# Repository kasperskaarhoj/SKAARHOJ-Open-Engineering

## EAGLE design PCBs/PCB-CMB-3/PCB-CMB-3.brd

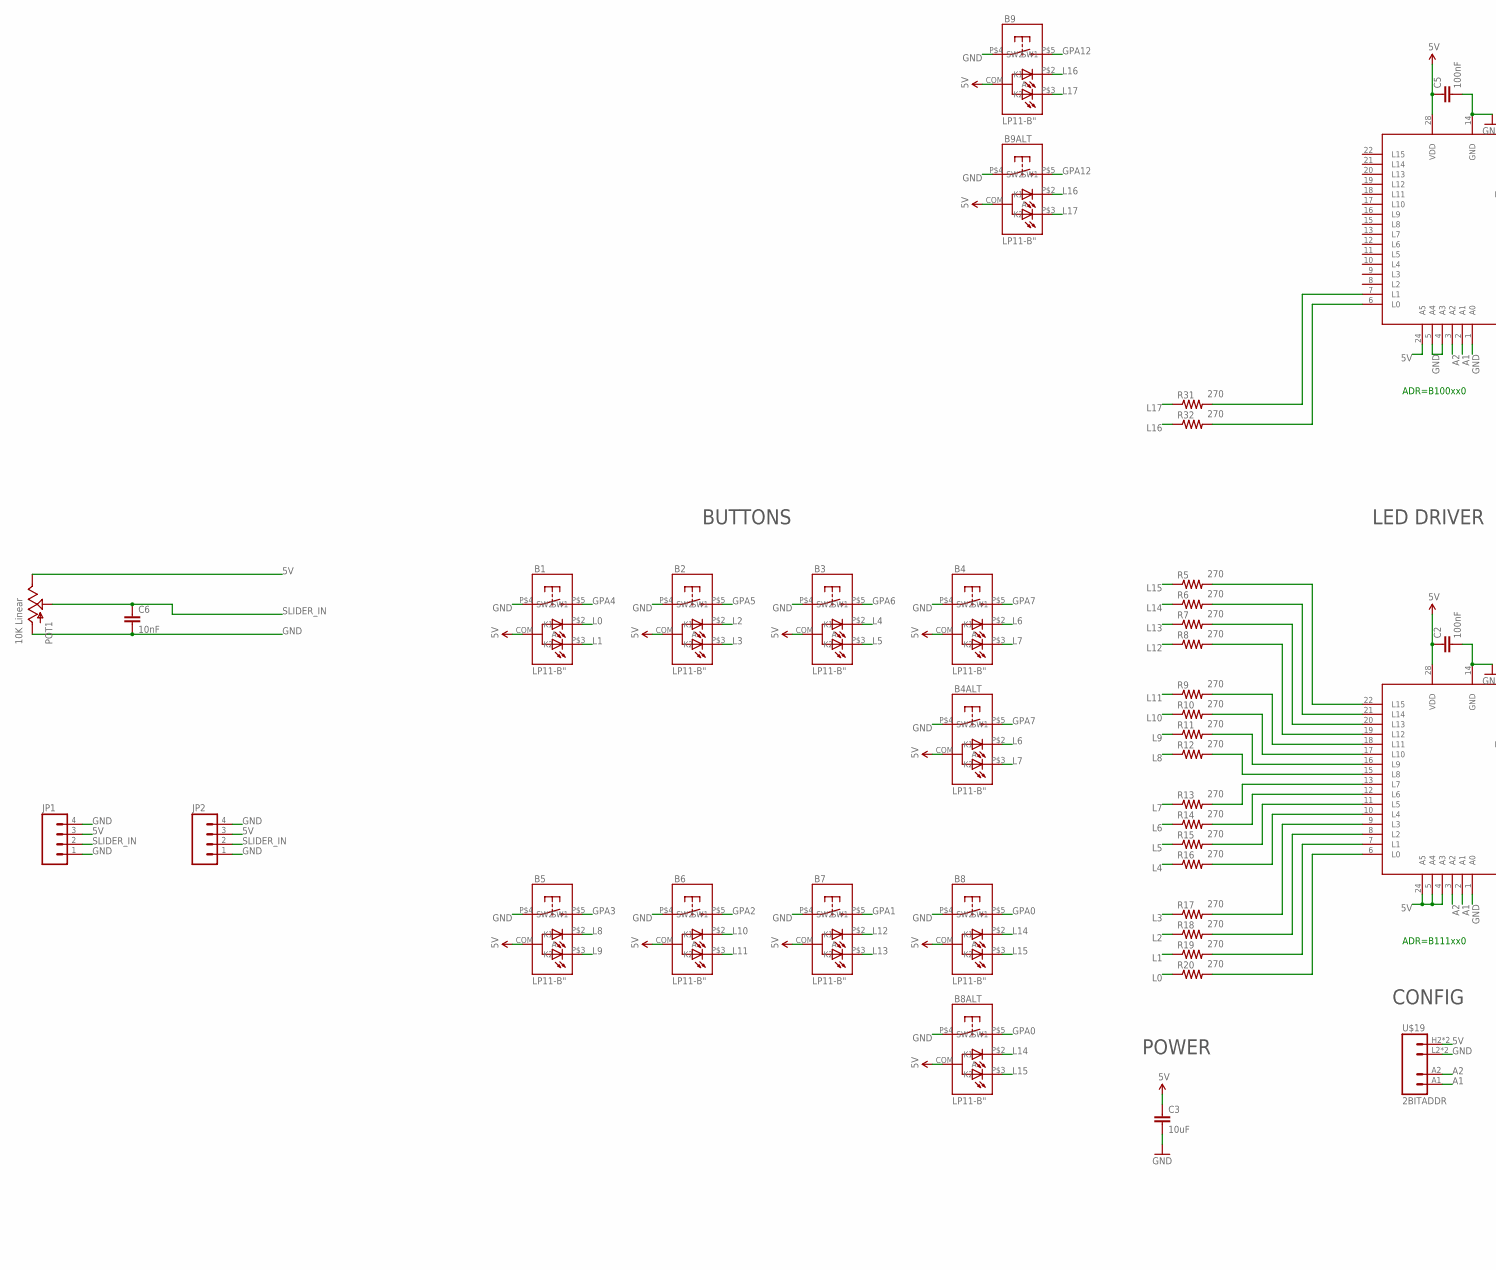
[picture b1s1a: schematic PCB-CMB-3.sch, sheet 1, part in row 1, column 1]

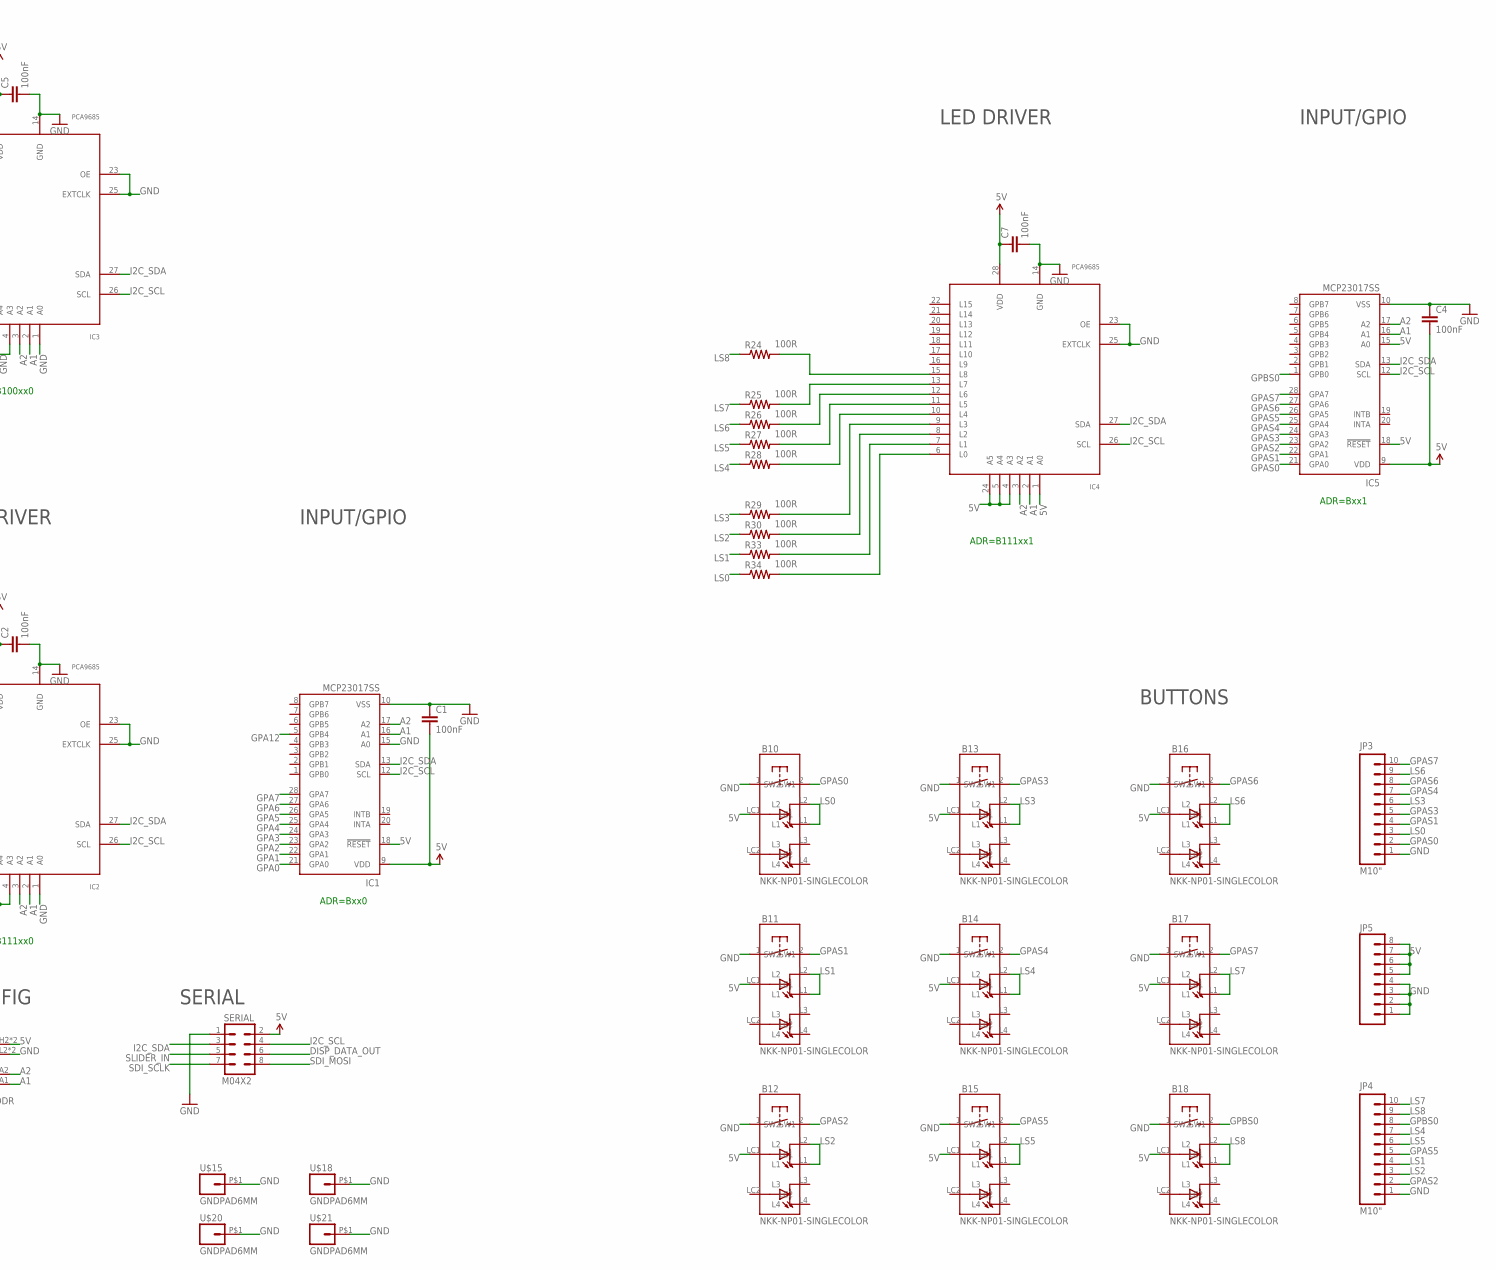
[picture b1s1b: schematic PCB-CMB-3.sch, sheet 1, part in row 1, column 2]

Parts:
B1, B2, B3, B4, B4ALT, B5, B6, B7, B8, B8ALT, B9, B9ALT: LP11-B"; LP11
B10, B11, B12, B13, B14, B15, B16, B17, B18: NKK-NP01-SINGLECOLOR; NKK-NP01
C1, C2, C4, C5, C7: 100nF; 0603-CAP
C3: 10uF; 0805
C6: 10nF; 0603-CAP
IC1, IC5: MCP23017SS; SSOP28; MPN MCP23017-E/SS
IC2, IC3, IC4: PCA9685; TSSOP28
JP1, JP2: M04PTH; 1X04
JP3, JP4: M10"; 1X10
JP5: M08LOCK; 1X08_LOCK
POT1: 10K Linear; SLIDER20
R5, R6, R7, R8, R9, R10, R11, R12, R13, R14, R15, R16, R17, R18, R19, R20, R31, R32: 270; 0603-RES
R24, R25, R26, R27, R28, R29, R30, R33, R34: 100R; 0603-RES
SERIAL: M04X2; 2X4
U$15, U$18, U$20, U$21: GNDPAD6MM; 3.2MMPAD6MM
U$19: 2BITADDR

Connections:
5V: B1.COM (A), B2.COM (A), B3.COM (A), B4.COM (A), B4ALT.COM (A), B5.COM (A), B6.COM (A), B7.COM (A), B8.COM (A), B8ALT.COM (A), B9.COM (A), B9ALT.COM (A), B10.LC1, B11.LC1, B12.LC1, B13.LC1, B14.LC1, B15.LC1, B16.LC1, B17.LC1, B18.LC1, C1.2, C2.1, C3.1, C4.2, C5.1, C7.1, IC1.9 (VDD), IC1.18 (!RESET), IC2.4 (A3), IC2.5 (A4), IC2.24 (A5), IC2.28 (VDD), IC3.24 (A5), IC3.28 (VDD), IC4.1 (A0), IC4.4 (A3), IC4.5 (A4), IC4.24 (A5), IC4.28 (VDD), IC5.9 (VDD), IC5.15 (A0), IC5.18 (!RESET), JP1.3, JP2.3, JP5.5, JP5.6, JP5.7, JP5.8, POT1.1 (E), SERIAL.2, U$19.H2 (VCC), U$19.H3 (VCC)
A1: IC1.16 (A1), IC2.2 (A1), IC3.2 (A1), IC4.2 (A1), IC5.16 (A1), U$19.A1
A2: IC1.17 (A2), IC2.3 (A2), IC3.3 (A2), IC4.3 (A2), IC5.17 (A2), U$19.A2
DISP_DATA_OUT: SERIAL.6
GND: B1.P$4 (SW1), B2.P$4 (SW1), B3.P$4 (SW1), B4.P$4 (SW1), B4ALT.P$4 (SW1), B5.P$4 (SW1), B6.P$4 (SW1), B7.P$4 (SW1), B8.P$4 (SW1), B8ALT.P$4 (SW1), B9.P$4 (SW1), B9ALT.P$4 (SW1), B10.1 (SW1), B11.1 (SW1), B12.1 (SW1), B13.1 (SW1), B14.1 (SW1), B15.1 (SW1), B16.1 (SW1), B17.1 (SW1), B18.1 (SW1), C1.1, C2.2, C3.2, C4.1, C5.2, C6.2, C7.2, IC1.10 (VSS), IC1.15 (A0), IC2.1 (A0), IC2.14 (GND), IC2.23 (OE), IC2.25 (EXTCLK), IC3.1 (A0), IC3.4 (A3), IC3.5 (A4), IC3.14 (GND), IC3.23 (OE), IC3.25 (EXTCLK), IC4.14 (GND), IC4.23 (OE), IC4.25 (EXTCLK), IC5.10 (VSS), JP1.1, JP1.4, JP2.1, JP2.4, JP3.1, JP4.1, JP5.1, JP5.2, JP5.3, JP5.4, POT1.3 (A), SERIAL.1, U$15.P$1, U$18.P$1, U$19.L2 (GND), U$19.L3 (GND), U$20.P$1, U$21.P$1
GPA0: B8.P$5 (SW2), B8ALT.P$5 (SW2), IC1.21 (GPA0)
GPA1: B7.P$5 (SW2), IC1.22 (GPA1)
GPA2: B6.P$5 (SW2), IC1.23 (GPA2)
GPA3: B5.P$5 (SW2), IC1.24 (GPA3)
GPA4: B1.P$5 (SW2), IC1.25 (GPA4)
GPA5: B2.P$5 (SW2), IC1.26 (GPA5)
GPA6: B3.P$5 (SW2), IC1.27 (GPA6)
GPA7: B4.P$5 (SW2), B4ALT.P$5 (SW2), IC1.28 (GPA7)
GPA12: B9.P$5 (SW2), B9ALT.P$5 (SW2), IC1.5 (GPB4)
GPAS0: B10.2 (SW2), IC5.21 (GPA0), JP3.2
GPAS1: B11.2 (SW2), IC5.22 (GPA1), JP3.4
GPAS2: B12.2 (SW2), IC5.23 (GPA2), JP4.2
GPAS3: B13.2 (SW2), IC5.24 (GPA3), JP3.5
GPAS4: B14.2 (SW2), IC5.25 (GPA4), JP3.7
GPAS5: B15.2 (SW2), IC5.26 (GPA5), JP4.5
GPAS6: B16.2 (SW2), IC5.27 (GPA6), JP3.8
GPAS7: B17.2 (SW2), IC5.28 (GPA7), JP3.10
GPBS0: B18.2 (SW2), IC5.1 (GPB0), JP4.8
I2C_SCL: IC1.12 (SCL), IC2.26 (SCL), IC3.26 (SCL), IC4.26 (SCL), IC5.12 (SCL), SERIAL.4
I2C_SDA: IC1.13 (SDA), IC2.27 (SDA), IC3.27 (SDA), IC4.27 (SDA), IC5.13 (SDA), SERIAL.3
L0: B1.P$2 (K1), R20.1
L1: B1.P$3 (K2), R19.1
L2: B2.P$2 (K1), R18.1
L3: B2.P$3 (K2), R17.1
L4: B3.P$2 (K1), R16.1
L5: B3.P$3 (K2), R15.1
L6: B4.P$2 (K1), B4ALT.P$2 (K1), R14.1
L7: B4.P$3 (K2), B4ALT.P$3 (K2), R13.1
L8: B5.P$2 (K1), R12.1
L9: B5.P$3 (K2), R11.1
L10: B6.P$2 (K1), R10.1
L11: B6.P$3 (K2), R9.1
L12: B7.P$2 (K1), R8.1
L13: B7.P$3 (K2), R7.1
L14: B8.P$2 (K1), B8ALT.P$2 (K1), R6.1
L15: B8.P$3 (K2), B8ALT.P$3 (K2), R5.1
L16: B9.P$2 (K1), B9ALT.P$2 (K1), R32.1
L17: B9.P$3 (K2), B9ALT.P$3 (K2), R31.1
LS0: B10.L1, B10.L2, JP3.3, R34.1
LS1: B11.L1, B11.L2, JP4.4, R33.1
LS2: B12.L1, B12.L2, JP4.3, R30.1
LS3: B13.L1, B13.L2, JP3.6, R29.1
LS4: B14.L1, B14.L2, JP4.7, R28.1
LS5: B15.L1, B15.L2, JP4.6, R27.1
LS6: B16.L1, B16.L2, JP3.9, R26.1
LS7: B17.L1, B17.L2, JP4.10, R25.1
LS8: B18.L1, B18.L2, JP4.9, R24.1
unnamed: IC4.13 (L7), R25.2
unnamed: IC4.12 (L6), R26.2
unnamed: IC4.11 (L5), R27.2
unnamed: IC2.13 (L7), R13.2
unnamed: IC2.12 (L6), R14.2
unnamed: IC4.10 (L4), R28.2
unnamed: IC2.11 (L5), R15.2
unnamed: IC4.9 (L3), R29.2
unnamed: IC2.10 (L4), R16.2
unnamed: IC2.9 (L3), R17.2
unnamed: IC2.8 (L2), R18.2
unnamed: IC2.7 (L1), R19.2
unnamed: IC4.8 (L2), R30.2
unnamed: IC3.7 (L1), R31.2
unnamed: IC3.6 (L0), R32.2
unnamed: IC4.7 (L1), R33.2
unnamed: IC4.6 (L0), R34.2
unnamed: IC4.15 (L8), R24.2
unnamed: IC2.6 (L0), R20.2
unnamed: IC2.15 (L8), R12.2
unnamed: IC2.16 (L9), R11.2
unnamed: IC2.17 (L10), R10.2
unnamed: IC2.18 (L11), R9.2
unnamed: IC2.19 (L12), R8.2
unnamed: IC2.20 (L13), R7.2
unnamed: IC2.21 (L14), R6.2
unnamed: IC2.22 (L15), R5.2
SDI_MOSI: SERIAL.8
SDI_SCLK: SERIAL.7
SLIDER_IN: C6.1, JP1.2, JP2.2, POT1.2A (S), SERIAL.5

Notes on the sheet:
ADR=B111xx0
ADR=Bxx0
BUTTONS
LED DRIVER
INPUT/GPIO
POWER
SERIAL
CONFIG
ADR=B100xx0
ADR=B111xx1
ADR=Bxx1

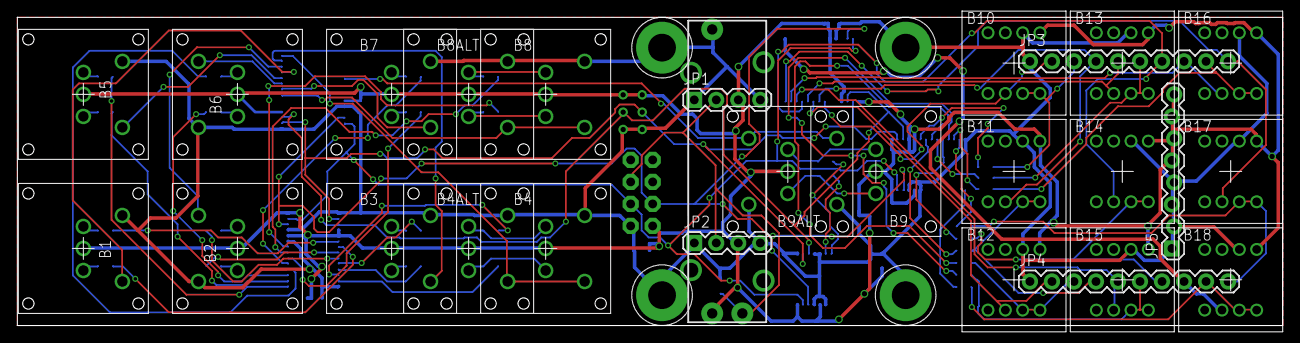
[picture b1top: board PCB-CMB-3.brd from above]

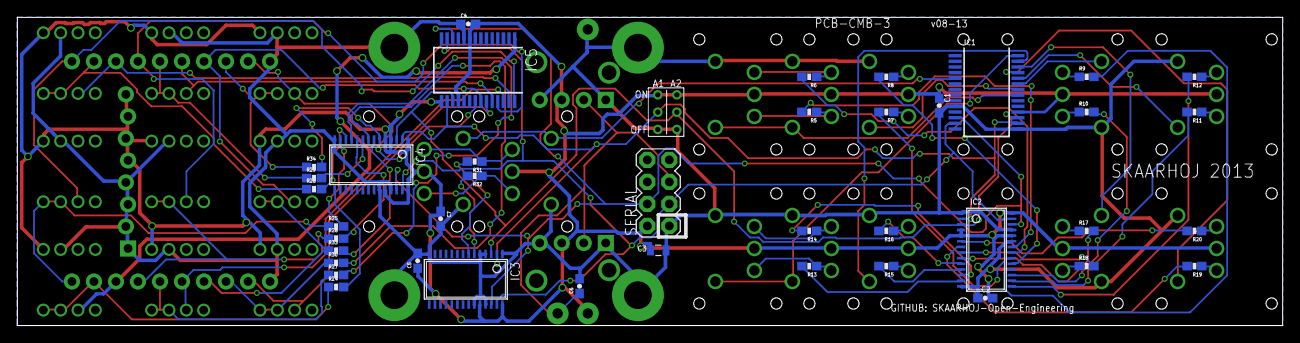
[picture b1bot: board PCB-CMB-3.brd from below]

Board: 2 copper layers, 146.0 x 35.6 mm, 72 parts (41 on the bottom side), 79 nets.

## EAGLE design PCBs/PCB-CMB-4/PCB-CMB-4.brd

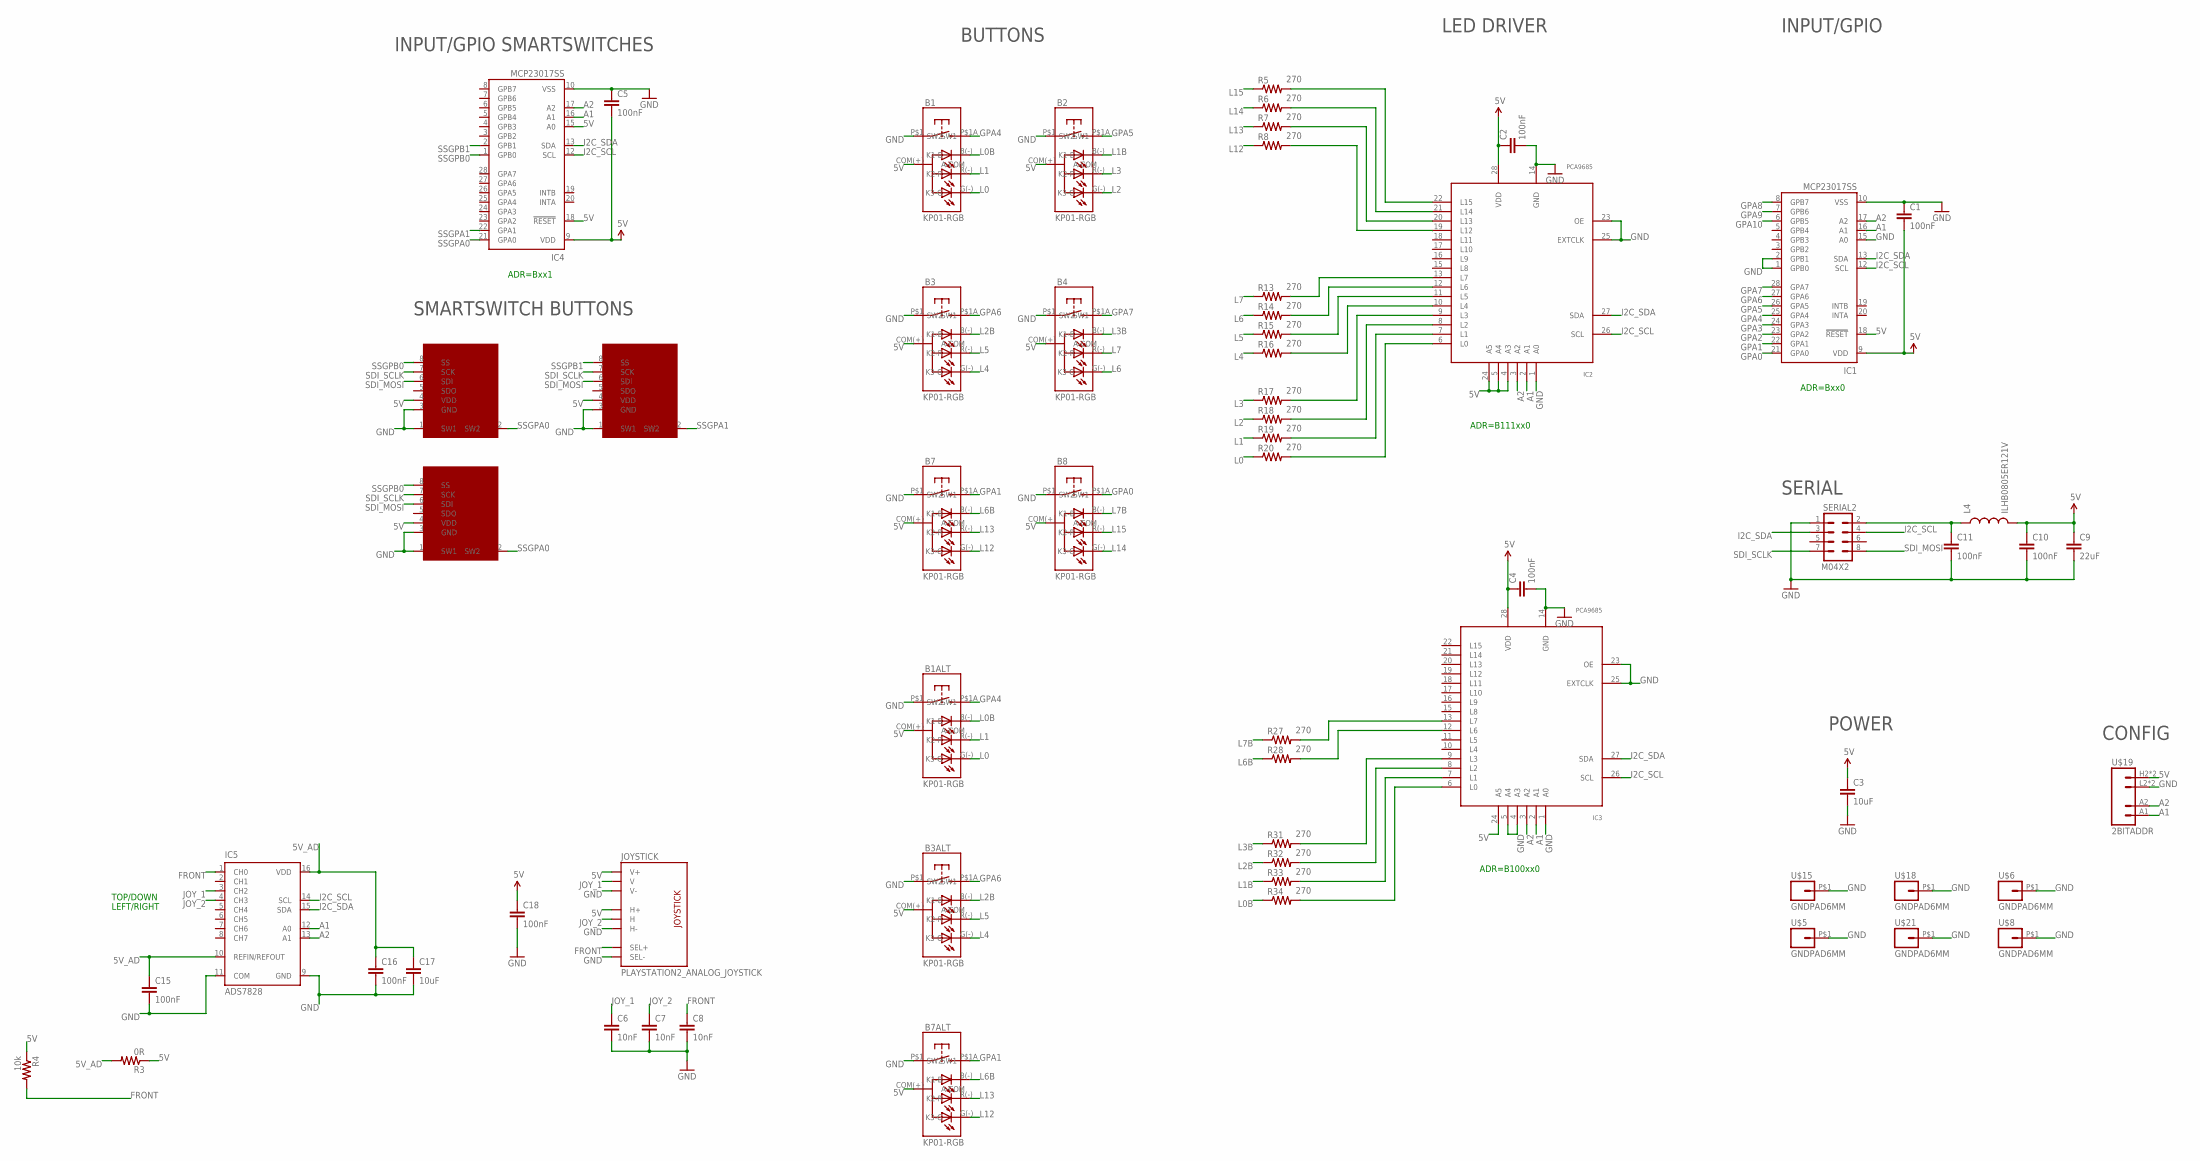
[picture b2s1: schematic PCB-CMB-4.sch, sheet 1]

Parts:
B1, B1ALT, B2, B3, B3ALT, B4, B7, B7ALT, B8: KP01-RGB; NKK-KP01
C1, C2, C4, C5, C10, C11, C15, C16, C18: 100nF; 0603-CAP
C3, C17: 10uF; 0805
C6, C7, C8: 10nF; 0603-CAP
C9: 22uF; 0805
IC1, IC4: MCP23017SS; SSOP28; MPN MCP23017-E/SS
IC2, IC3: PCA9685; TSSOP28
IC5: ADS7828; TSSOP16-PW
JOYSTICK: PLAYSTATION2_ANALOG_JOYSTICK
L4: ILHB0805ER121V; 0805
R3: 0R; 0603-RES
R4: 10k; 0603-RES
R5, R6, R7, R8, R13, R14, R15, R16, R17, R18, R19, R20, R27, R28, R31, R32, R33, R34: 270; 0603-RES
SERIAL2: M04X2; 2X4
SSW1, SSW1ALT, SSW2: SMART_SWITCHSMART_SWITCH_8PIN; SMART_SWITCH
U$5, U$6, U$8, U$15, U$18, U$21: GNDPAD6MM; 3.2MMPAD6MM
U$19: 2BITADDR

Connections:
5V: B1.COM(+) (A-COM), B1ALT.COM(+) (A-COM), B2.COM(+) (A-COM), B3.COM(+) (A-COM), B3ALT.COM(+) (A-COM), B4.COM(+) (A-COM), B7.COM(+) (A-COM), B7ALT.COM(+) (A-COM), B8.COM(+) (A-COM), C1.2, C2.1, C3.1, C4.1, C5.2, C9.1, C10.1, C18.1, IC1.9 (VDD), IC1.18 (!RESET), IC2.4 (A3), IC2.5 (A4), IC2.24 (A5), IC2.28 (VDD), IC3.24 (A5), IC3.28 (VDD), IC4.9 (VDD), IC4.15 (A0), IC4.18 (!RESET), JOYSTICK.H1 (H+), JOYSTICK.V1 (V+), L4.2, R3.1, R4.1, SSW1.4 (VDD), SSW1ALT.4 (VDD), SSW2.4 (VDD), U$19.H2 (VCC), U$19.H3 (VCC)
5V_AD: C15.1, C16.1, C17.1, IC5.10 (REFIN/REFOUT), IC5.16 (VDD), R3.2
A1: IC1.16 (A1), IC2.2 (A1), IC3.2 (A1), IC4.16 (A1), IC5.12 (A0), U$19.A1
A2: IC1.17 (A2), IC2.3 (A2), IC3.3 (A2), IC4.17 (A2), IC5.13 (A1), U$19.A2
FRONT: C8.1, IC5.1 (CH0), JOYSTICK.B1A (SEL+), R4.2
GND: B1.P$1 (SW1), B1ALT.P$1 (SW1), B2.P$1 (SW1), B3.P$1 (SW1), B3ALT.P$1 (SW1), B4.P$1 (SW1), B7.P$1 (SW1), B7ALT.P$1 (SW1), B8.P$1 (SW1), C1.1, C2.2, C3.2, C4.2, C5.1, C6.2, C7.2, C8.2, C9.2, C10.2, C11.2, C15.2, C16.2, C17.2, C18.2, IC1.1 (GPB0), IC1.2 (GPB1), IC1.10 (VSS), IC1.15 (A0), IC2.1 (A0), IC2.14 (GND), IC2.23 (OE), IC2.25 (EXTCLK), IC3.1 (A0), IC3.4 (A3), IC3.5 (A4), IC3.14 (GND), IC3.23 (OE), IC3.25 (EXTCLK), IC4.10 (VSS), IC5.9 (GND), IC5.11 (COM), JOYSTICK.B2A (SEL-), JOYSTICK.H3 (H-), JOYSTICK.V3 (V-), SERIAL2.1, SSW1.1 (SW1), SSW1.3 (GND), SSW1ALT.1 (SW1), SSW1ALT.3 (GND), SSW2.1 (SW1), SSW2.3 (GND), U$5.P$1, U$6.P$1, U$8.P$1, U$15.P$1, U$18.P$1, U$19.L2 (GND), U$19.L3 (GND), U$21.P$1
GPA0: B8.P$1A (SW2), IC1.21 (GPA0)
GPA1: B7.P$1A (SW2), B7ALT.P$1A (SW2), IC1.22 (GPA1)
GPA2: IC1.23 (GPA2)
GPA3: IC1.24 (GPA3)
GPA4: B1.P$1A (SW2), B1ALT.P$1A (SW2), IC1.25 (GPA4)
GPA5: B2.P$1A (SW2), IC1.26 (GPA5)
GPA6: B3.P$1A (SW2), B3ALT.P$1A (SW2), IC1.27 (GPA6)
GPA7: B4.P$1A (SW2), IC1.28 (GPA7)
GPA8: IC1.8 (GPB7)
GPA9: IC1.7 (GPB6)
GPA10: IC1.6 (GPB5)
I2C_SCL: IC1.12 (SCL), IC2.26 (SCL), IC3.26 (SCL), IC4.12 (SCL), IC5.14 (SCL), SERIAL2.4
I2C_SDA: IC1.13 (SDA), IC2.27 (SDA), IC3.27 (SDA), IC4.13 (SDA), IC5.15 (SDA), SERIAL2.3
JOY_1: C6.1, IC5.3 (CH2), JOYSTICK.V2 (V)
JOY_2: C7.1, IC5.4 (CH3), JOYSTICK.H2 (H)
L0: B1.G(-) (K3-G), B1ALT.G(-) (K3-G), R20.1
L0B: B1.B(-) (K1-B), B1ALT.B(-) (K1-B), R34.1
L1: B1.R(-) (K2-R), B1ALT.R(-) (K2-R), R19.1
L1B: B2.B(-) (K1-B), R33.1
L2: B2.G(-) (K3-G), R18.1
L2B: B3.B(-) (K1-B), B3ALT.B(-) (K1-B), R32.1
L3: B2.R(-) (K2-R), R17.1
L3B: B4.B(-) (K1-B), R31.1
L4: B3.G(-) (K3-G), B3ALT.G(-) (K3-G), R16.1
L5: B3.R(-) (K2-R), B3ALT.R(-) (K2-R), R15.1
L6: B4.G(-) (K3-G), R14.1
L6B: B7.B(-) (K1-B), B7ALT.B(-) (K1-B), R28.1
L7: B4.R(-) (K2-R), R13.1
L7B: B8.B(-) (K1-B), R27.1
L12: B7.G(-) (K3-G), B7ALT.G(-) (K3-G), R8.1
L13: B7.R(-) (K2-R), B7ALT.R(-) (K2-R), R7.1
L14: B8.G(-) (K3-G), R6.1
L15: B8.R(-) (K2-R), R5.1
unnamed: C11.1, L4.1, SERIAL2.2
unnamed: IC3.13 (L7), R27.2
unnamed: IC3.12 (L6), R28.2
unnamed: IC2.13 (L7), R13.2
unnamed: IC2.12 (L6), R14.2
unnamed: IC2.11 (L5), R15.2
unnamed: IC2.10 (L4), R16.2
unnamed: IC2.9 (L3), R17.2
unnamed: IC2.8 (L2), R18.2
unnamed: IC2.7 (L1), R19.2
unnamed: IC3.9 (L3), R31.2
unnamed: IC3.8 (L2), R32.2
unnamed: IC3.7 (L1), R33.2
unnamed: IC3.6 (L0), R34.2
unnamed: IC2.6 (L0), R20.2
unnamed: IC2.19 (L12), R8.2
unnamed: IC2.20 (L13), R7.2
unnamed: IC2.21 (L14), R6.2
unnamed: IC2.22 (L15), R5.2
SDI_MOSI: SERIAL2.8, SSW1.6 (SDI), SSW1ALT.6 (SDI), SSW2.6 (SDI)
SDI_SCLK: SERIAL2.7, SSW1.7 (SCK), SSW1ALT.7 (SCK), SSW2.7 (SCK)
SSGPA0: IC4.21 (GPA0), SSW1.2 (SW2), SSW1ALT.2 (SW2)
SSGPA1: IC4.22 (GPA1), SSW2.2 (SW2)
SSGPB0: IC4.1 (GPB0), SSW1.8 (SS), SSW1ALT.8 (SS)
SSGPB1: IC4.2 (GPB1), SSW2.8 (SS)

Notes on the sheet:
ADR=B111xx0
ADR=Bxx0
BUTTONS
LED DRIVER
INPUT/GPIO
POWER
ADR=B100xx0
ADR=Bxx1
INPUT/GPIO SMARTSWITCHES
SMARTSWITCH BUTTONS
CONFIG
SERIAL
TOP/DOWN
LEFT/RIGHT

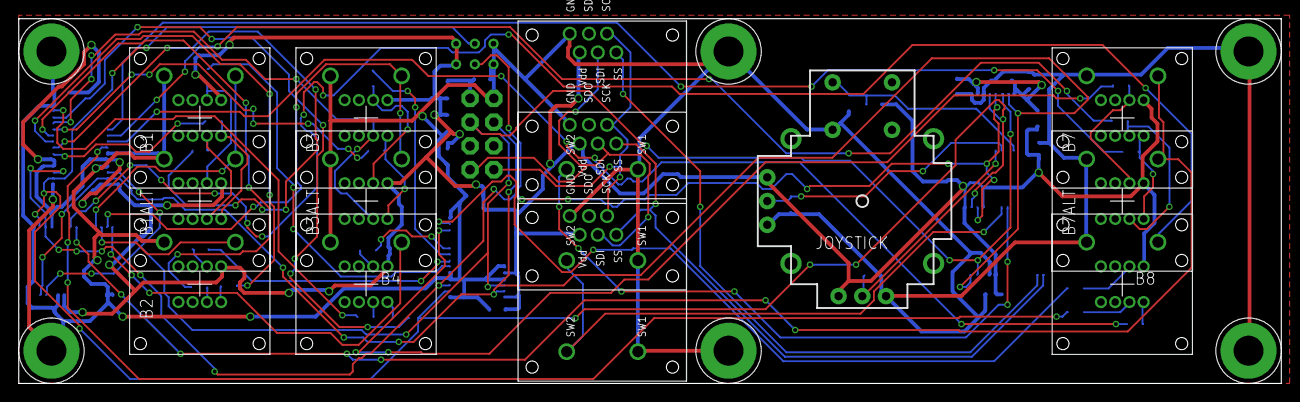
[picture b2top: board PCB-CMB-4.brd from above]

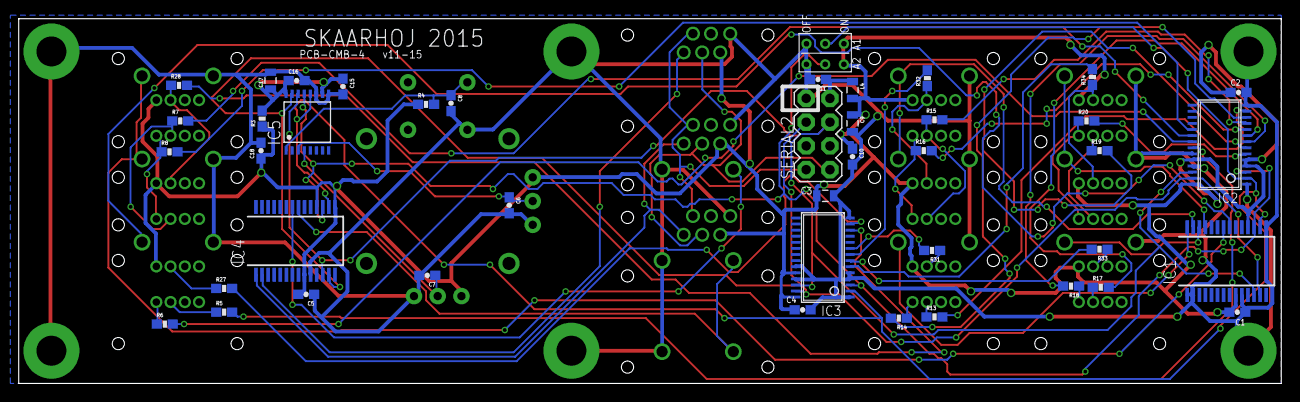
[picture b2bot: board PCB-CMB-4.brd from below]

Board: 2 copper layers, 135.0 x 39.0 mm, 62 parts (43 on the bottom side), 59 nets.

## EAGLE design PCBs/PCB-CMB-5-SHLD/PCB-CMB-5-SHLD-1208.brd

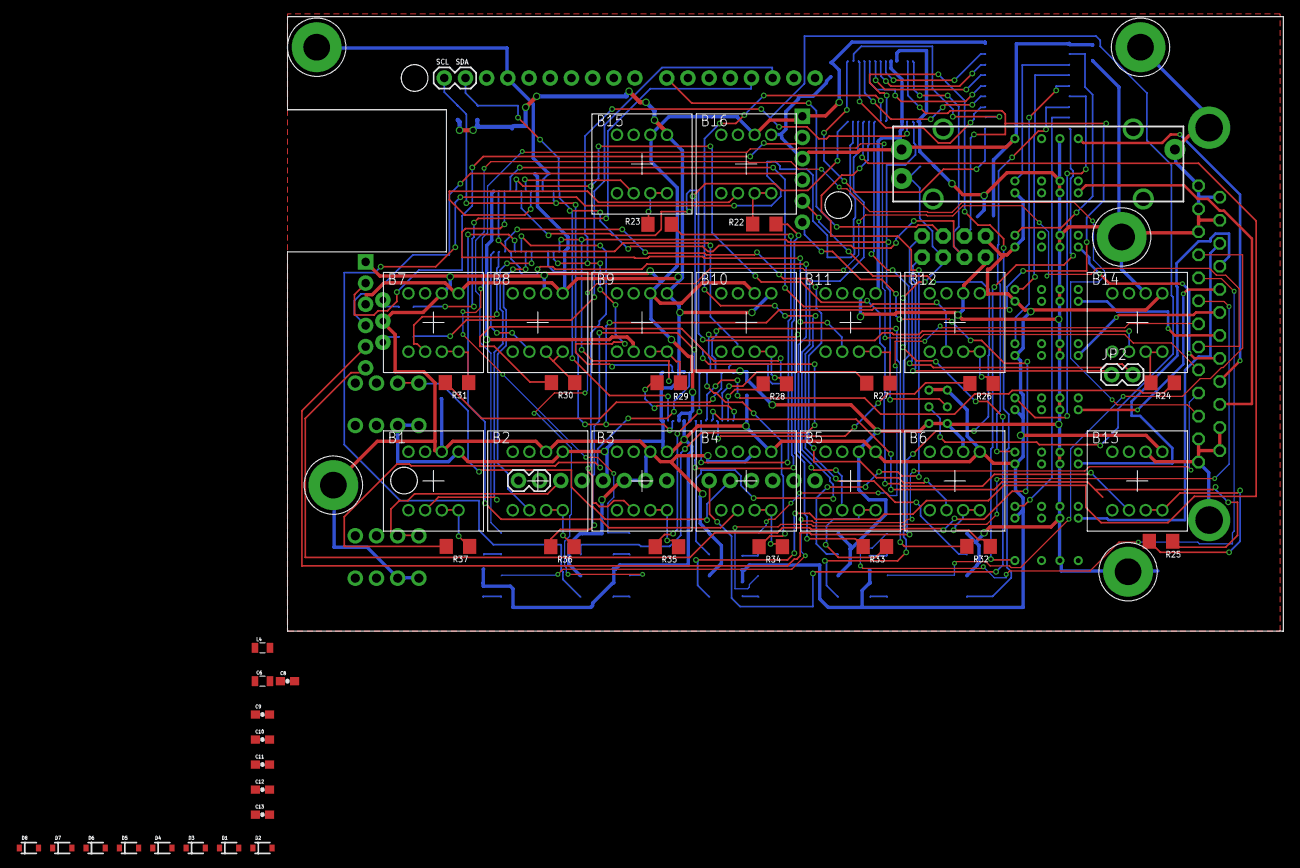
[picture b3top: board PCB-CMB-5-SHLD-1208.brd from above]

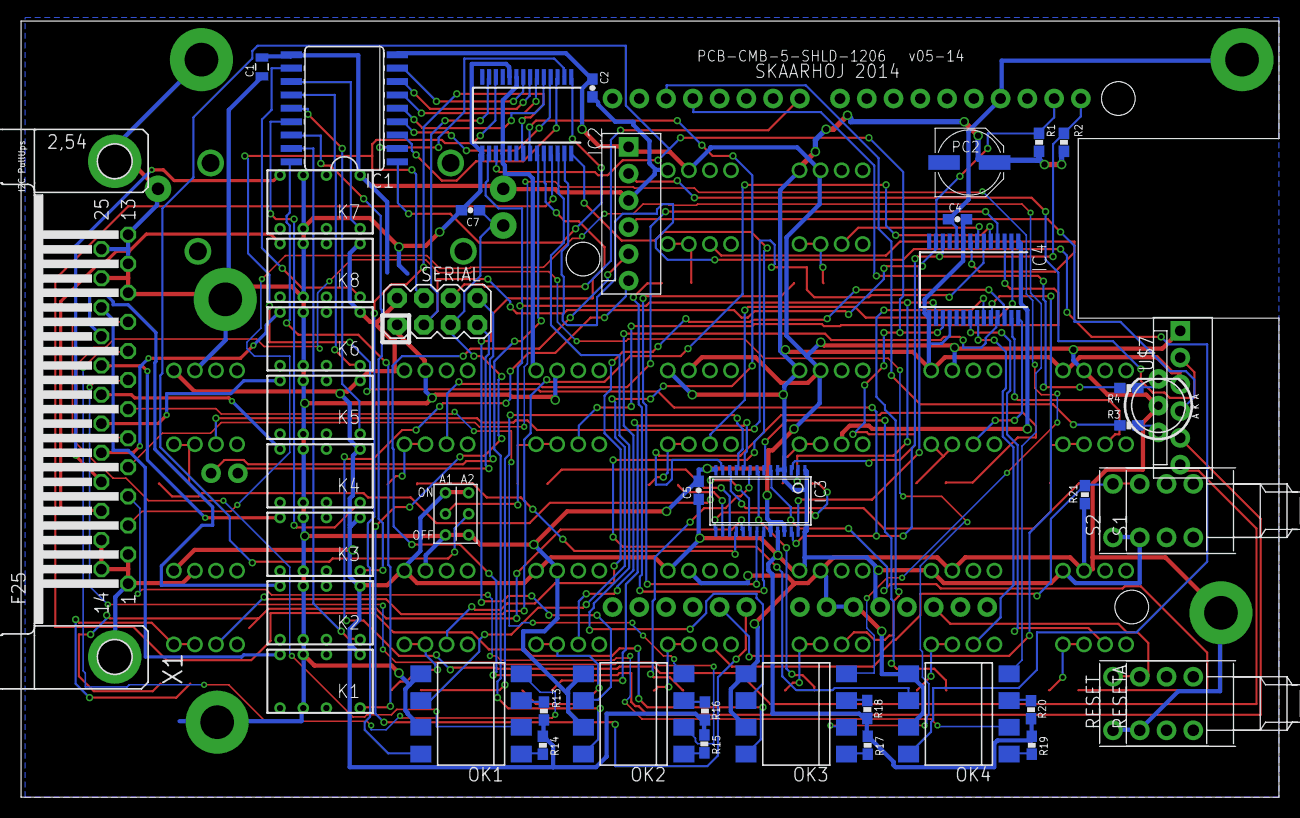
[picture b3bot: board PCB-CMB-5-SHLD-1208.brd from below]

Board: 2 copper layers, 119.4 x 73.7 mm, 103 parts (45 on the bottom side), 117 nets.

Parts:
B1, B2, B3, B4, B5, B6, B7, B8, B9, B10, B11, B12, B13, B14, B15, B16: NKK-NP01-SINGLECOLOR; NKK-NP01
C1: 100nF; 0805
C2, C4, C5, C8, C9, C10, C11, C12, C13: 100nF; 0603-CAP
C6: 22uF; 0805
C7: 10nF; 0603-CAP
D1, D2, D3, D4, D5, D6, D7, D8: 1N4148; SOD-323
GND: ARDUINO_SHIELDNO_SILK; DUEMILANOVE_VIAS
IC1: ULN2803A; SO18W
IC2, IC4: MCP23017SS; SSOP28
IC3: PCA9685; TSSOP28
JP1, JP2, JP4: 1X02
JP3, JP5: MOLEX-1X6
K1, K2, K3, K4, K5, K6, K7, K8: RELAY5VIM03; DS2Y
L4: ILHB0805ER121V; 0805
OK1, OK2, OK3, OK4: LTV826S; DIL8-SMD
PC2: 47u; PANASONIC_D
POT1: 10K Linear; SLIDER20
R1, R2: 1K5; 0603-RES
R3, R4: 270; 0603-RES
R13, R14, R15, R16, R17, R18, R19, R20: 330R; 0603-RES
R21: 10K; 0603-RES
R22, R23, R24, R25, R26, R27, R28, R29, R30, R31, R32, R33, R34, R35, R36, R37: 100R; 1206
RESET: PUSHBUTTON
RESETA: PUSHBUTTON
S1, S2: PUSHBUTTON
SERIAL: M04X2; 2X4
U$4, U$15, U$18, U$20, U$21: GNDPAD6MM; 3.2MMPAD6MM
U$7: LEDBICOLOR-AKA; LED5MM-BICOLOR
U$19: 2BITADDR
X1: DB25F; F25HP

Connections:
5V: B1.LC1, B2.LC1, B3.LC1, B4.LC1, B5.LC1, B6.LC1, B7.LC1, B8.LC1, B9.LC1, B10.LC1, B11.LC1, B12.LC1, B13.LC1, B14.LC1, B15.LC1, B16.LC1, C1.2, C2.2, C4.2, C5.1, C6.1, C8.1, C10.1, C11.1, C12.1, C13.1, IC1.10, IC2.9, IC2.18, IC3.1, IC3.4, IC3.5, IC3.24, IC3.28, IC4.9, IC4.15, IC4.18, JP3.3, JP5.3, K1.1, K2.1, K3.1, K4.1, K5.1, K6.1, K7.1, K8.1, L4.2, POT1.1, R1.2, R2.2, R13.1, R14.1, R15.1, R16.1, R17.1, R18.1, R19.1, R20.1, S1.3, S2.3, U$19.H2, U$19.H3
A1: IC2.16, IC3.2, IC4.16, U$19.A1
A1CFG: GND.A1, R21.2, S1.1, S2.1
A2: IC2.17, IC3.3, IC4.17, U$19.A2
ARD_5V: C9.1, GND.5V, L4.1, PC2.+, SERIAL.2
D2: GND.D2, R3.2
D3: GND.D3, R4.2
DISP_DATA_OUT: GND.D7, SERIAL.6
GND: B1.1, B2.1, B3.1, B4.1, B5.1, B6.1, B7.1, B8.1, B9.1, B10.1, B11.1, B12.1, B13.1, B14.1, B15.1, B16.1, C1.1, C2.1, C4.1, C5.2, C6.2, C7.2, C8.2, C9.2, C10.2, C11.2, C12.2, C13.2, GND.GND@0, GND.GND@1, GND.GND@2, IC1.9, IC2.10, IC2.15, IC3.14, IC3.23, IC3.25, IC4.10, JP3.1, JP5.1, K1.P1, K1.P2, K2.P1, K2.P2, K3.P1, K3.P2, K4.P1, K4.P2, K5.P1, K5.P2, K6.P1, K6.P2, K7.P1, K7.P2, K8.P1, K8.P2, OK1.5, OK1.7, OK2.5, OK2.7, OK3.5, OK3.7, OK4.5, OK4.7, PC2.-, POT1.3, R21.1, RESET.3, RESETA.3, SERIAL.1, U$4.P$1, U$7.K1, U$15.P$1, U$18.P$1, U$19.L2, U$19.L3, U$20.P$1, U$21.P$1, X1.1, X1.2, X1.11, X1.12, X1.13, X1.14, X1.15, X1.24, X1.25, X1.G1, X1.G2
GPA0: B1.2, IC4.21
GPA1: B2.2, IC4.22
GPA2: B3.2, IC4.23
GPA3: B4.2, IC4.24
GPA4: B5.2, IC4.25
GPA5: B6.2, IC4.26
GPA6: B7.2, IC4.27
GPA7: B8.2, IC4.28
GPB0: B9.2, IC4.1
GPB1: B10.2, IC4.2
GPB2: B11.2, IC4.3
GPB3: B12.2, IC4.4
GPB4: B13.2, IC4.5
GPB5: B14.2, IC4.6
GPB6: B15.2, IC4.7
GPB7: B16.2, IC4.8
I2C_SCL: IC2.12, IC3.26, IC4.12, JP4.2, R2.1, SERIAL.4
I2C_SDA: IC2.13, IC3.27, IC4.13, JP4.1, R1.1, SERIAL.3
L0: B1.L1, B1.L2, R37.1
L1: B2.L1, B2.L2, R36.1
L2: B3.L1, B3.L2, R35.1
L3: B4.L1, B4.L2, R34.1
L4: B5.L1, B5.L2, R33.1
L5: B6.L1, B6.L2, R32.1
L6: B7.L1, B7.L2, R31.1
L7: B8.L1, B8.L2, R30.1
L8: B9.L1, B9.L2, R29.1
L9: B10.L1, B10.L2, R28.1
L10: B11.L1, B11.L2, R27.1
L11: B12.L1, B12.L2, R26.1
L12: B13.L1, B13.L2, R25.1
L13: B14.L1, B14.L2, R24.1
L14: B15.L1, B15.L2, R23.1
L15: B16.L1, B16.L2, R22.1
unnamed: K1.S1, X1.23
unnamed: IC3.13, R30.2
unnamed: JP3.4, JP5.4
unnamed: IC1.18, K1.16
unnamed: IC1.1, IC2.1
unnamed: K2.S1, X1.22
unnamed: R4.1, U$7.A2
unnamed: JP3.5, JP5.5
unnamed: IC1.17, K2.16
unnamed: K3.S1, X1.21
unnamed: R3.1, U$7.A3
unnamed: JP3.2, JP5.2
unnamed: IC1.16, K3.16
unnamed: K4.S1, X1.20
unnamed: IC1.15, K4.16
unnamed: K5.S1, X1.19
unnamed: IC3.12, R31.2
unnamed: IC1.14, K5.16
unnamed: K6.S1, X1.18
unnamed: IC3.11, R32.2
unnamed: IC1.13, K6.16
unnamed: K7.S1, X1.17
unnamed: IC1.12, K7.16
unnamed: K8.S1, X1.16
unnamed: IC3.10, R33.2
unnamed: IC1.11, K8.16
unnamed: IC1.2, IC2.2
unnamed: IC1.3, IC2.3
unnamed: IC1.4, IC2.4
unnamed: IC1.5, IC2.5
unnamed: IC1.6, IC2.6
unnamed: IC1.7, IC2.7
unnamed: IC1.8, IC2.8
unnamed: JP3.6, JP5.6
unnamed: D7.1, OK1.3, R13.2
unnamed: D8.1, OK1.1, R14.2
unnamed: D8.2, OK1.2, X1.10
unnamed: D6.1, OK2.1, R15.2
unnamed: IC2.21, OK1.8
unnamed: D5.1, OK2.3, R16.2
unnamed: D4.1, OK3.1, R17.2
unnamed: D3.1, OK3.3, R18.2
unnamed: D4.2, OK3.2, X1.6
unnamed: D1.1, OK4.1, R19.2
unnamed: D2.1, OK4.3, R20.2
unnamed: IC3.9, R34.2
unnamed: IC3.8, R35.2
unnamed: D7.2, OK1.4, X1.9
unnamed: D6.2, OK2.2, X1.8
unnamed: D5.2, OK2.4, X1.7
unnamed: IC2.28, OK4.6
unnamed: D3.2, OK3.4, X1.5
unnamed: D1.2, OK4.2, X1.4
unnamed: D2.2, OK4.4, X1.3
unnamed: IC3.7, R36.2
unnamed: IC2.22, OK1.6
unnamed: IC2.23, OK2.8
unnamed: IC2.24, OK2.6
unnamed: IC2.25, OK3.8
unnamed: IC2.26, OK3.6
unnamed: IC2.27, OK4.8
unnamed: IC3.6, R37.2
unnamed: IC3.15, R29.2
unnamed: IC3.16, R28.2
unnamed: IC3.17, R27.2
unnamed: IC3.18, R26.2
unnamed: IC3.19, R25.2
unnamed: IC3.20, R24.2
unnamed: IC3.21, R23.2
unnamed: IC3.22, R22.2
RES: GND.RES, RESET.1, RESETA.1
SDI_MOSI: JP2.2, SERIAL.8
SDI_SCLK: JP2.1, SERIAL.7
SLIDER_IN: C7.1, GND.A0, POT1.2A, SERIAL.5

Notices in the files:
parts and their libraries:
SparkFun: Licensing: CC v3.0 Share-Alike You are welcome to use this library for commercial purposes.
